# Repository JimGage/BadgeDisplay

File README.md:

# Badge Display

## Introduction
This was a bit of an art project that I did for SIGGRAPH 2018. Path tracing seemed to be a big theme that year and I wanted a badge that spent the day path tracing. The plan was that it would start off fuzzy in the morning and by the end of the day render a clear image.

## Images

The final badge

The images that were rendered during the first four days of the conference. Each image took around 10 hours on 72MHz ARM processor.

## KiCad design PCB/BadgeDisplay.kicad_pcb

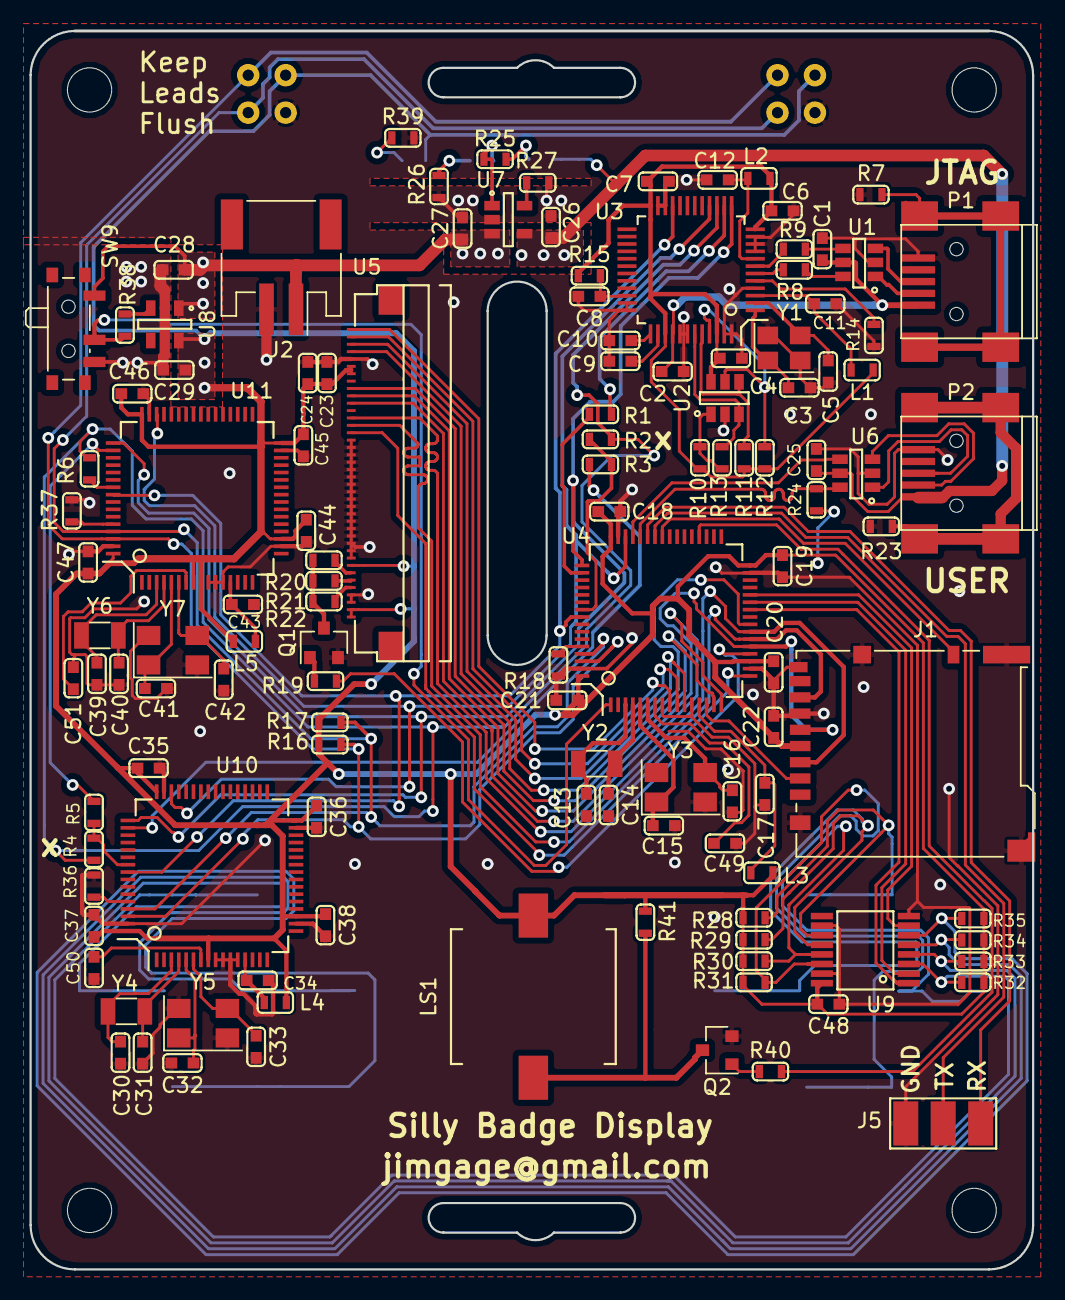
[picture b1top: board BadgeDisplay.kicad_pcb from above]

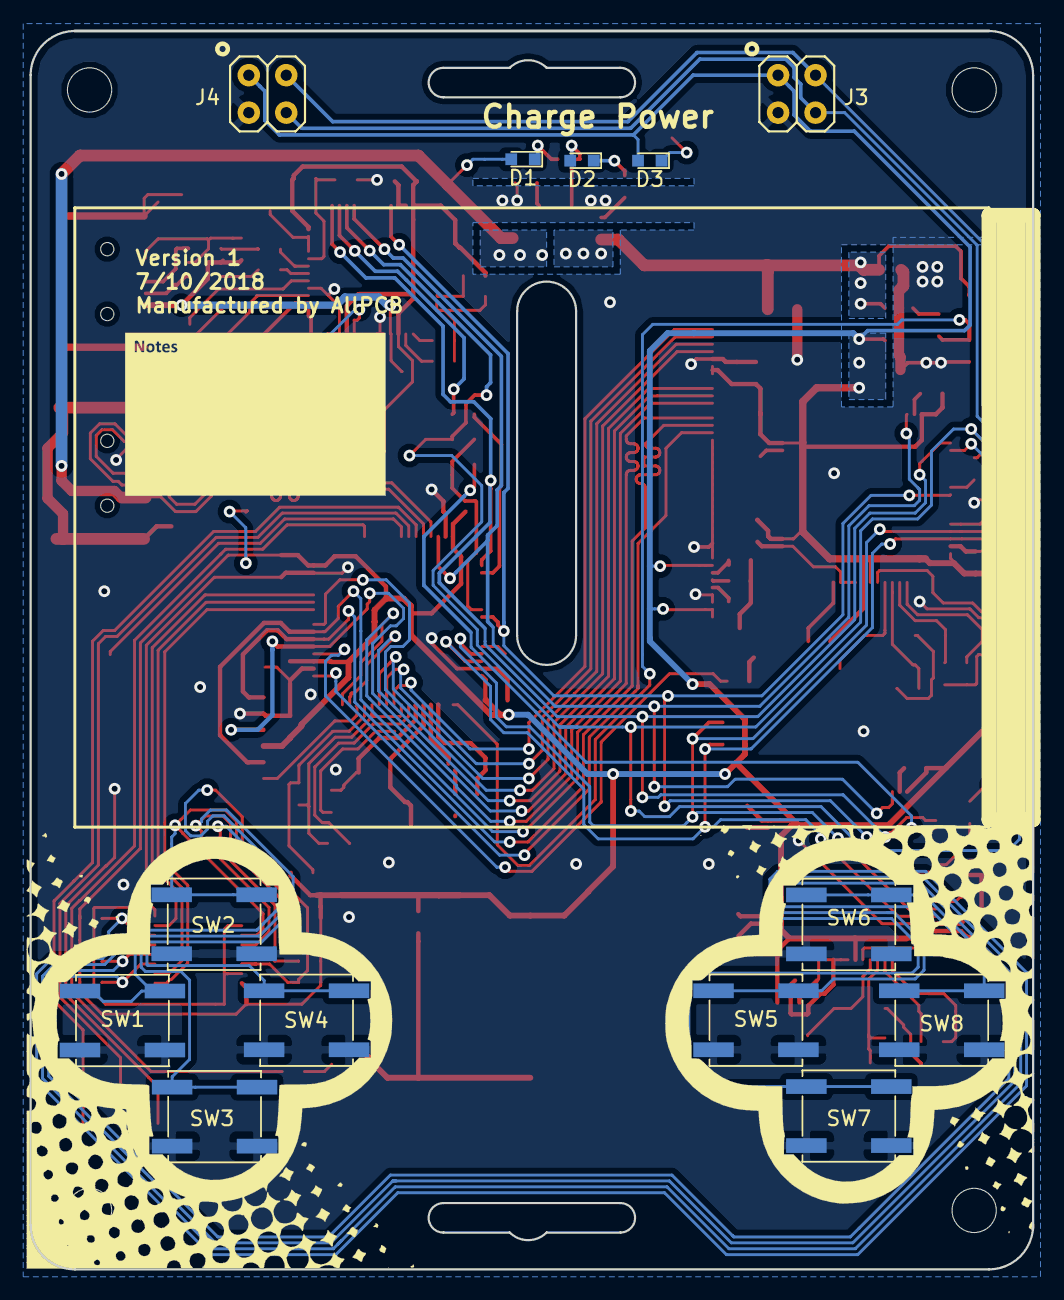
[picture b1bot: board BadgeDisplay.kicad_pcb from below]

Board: 2 copper layers, 68.0 x 84.0 mm, 137 parts (13 on the bottom side), 105 nets.

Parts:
C1, C4, C6, C7, C9, C10, C17, C18, C19, C20, C21, C22, C23, C25, C34, C35, C36, C37, C38, C43, C44, C45, C46, C47, C48, C49, C50, C51: 0u1; C_0603
C2, C11, C12, C26, C27, C28, C29: 4u7; C_0603
C3, C5: 16p; C_0603
C8: 10n; C_0603
C13, C14, C30, C31, C39, C40: 22p; C_0603
C15, C16, C32, C33, C41, C42: 36p; C_0603
C24: 1u; C_0603
D1, D2, D3: LED; LED_0603
J1: Micro_SD_Card_Det; Hirose_DM3BT-DSF-PEJS
J2: Conn_01x02; JST_PH_S2B-PH-SM4-TB_02x2.00mm_Angled
J3, J4: AddOn; AddOnConnector
J5: Conn_01x03; 3pin_smd
L1, L2, L3, L4, L5: Bead; L_0603
LS1: Speaker_Crystal; AST1109MLTRQ
P1, P2: USB_MINI; USB_Mini-B
Q1, Q2: MMBT3904; SOT-23
R1, R3, R5, R6: 0; R_0603
R2, R4: X; R_0603
R7, R23: 1; R_0603
R8, R9: 22; R_0603
R10, R11, R12, R15, R18, R28, R29, R30, R31, R32, R33, R34, R35, R36, R37: 10K; R_0603
R13: 2K; R_0603
R14: 12K; R_0603
R16, R17: 4k7; R_0603
R19, R40, R41: 1K; R_0603
R20, R21, R22, R38: 10; R_0603
R24: 1K5; R_0603
R25, R26: 470; R_0603
R27: 2k; R_0603
R39: 100; R_0603
SW1: LEFT_LEFT; SW_SPST_EVPBF
SW2: LEFT_UP; SW_SPST_EVPBF
SW3: LEFT_DOWN; SW_SPST_EVPBF
SW4: LEFT_RIGHT; SW_SPST_EVPBF
SW5: RIGHT_LEFT; SW_SPST_EVPBF
SW6: RIGHT_UP; SW_SPST_EVPBF
SW7: RIGHT_DOWN; SW_SPST_EVPBF
SW8: RIGHT_RIGHT; SW_SPST_EVPBF
SW9: SW_SPDT; SW_SPDT_PCM12
U1, U6: USBLC6-2; SOT-23-6
U2: 93LC56BT-OT; SOT-23-6
U3: FT232H; LQFP-48_7x7mm_Pitch0.5mm
U4, U10, U11: STM32F303RE-LQFP64; LQFP-64_10x10mm_Pitch0.5mm
U5: LCD_40PIN; 40Pin_conn_05Pitch
U7: MCP73831T; SOT-23-5
U8: TLV75733PDBVR; SOT-23-5
U9: 74HC165; TSSOP-16_4.4x5mm_Pitch0.65mm
Y1: 12MHz; Crystal_SMD_3225-4pin_3.2x2.5mm
Y2, Y4, Y6: 32.768KHz; Crystal_SMD_3215-2pin_3.2x1.5mm
Y3, Y5, Y7: 8MHz; Crystal_SMD_5032-4pin_5.0x3.2mm

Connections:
+3.3VA: C4.1, C6.1, C7.1, L1.2, L2.1, R10.1, R11.1, R12.1, R15.1, U2.6, U3.12, U3.24, U3.39, U3.46
+3V3: C18.1, C19.1, C20.1, C21.1, C22.1, C23.1, C24.1, C29.1, C35.1, C36.1, C37.1, C38.1, C44.1, C45.1, C46.1, C47.1, C48.1, D3.2, J1.4, J3.1, J4.1, L3.2, L4.2, L5.2, LS1.1, R16.1, R17.1, R24.1, R28.1, R29.1, R30.1, R31.1, R32.1, R33.1, R34.1, R35.1, R41.1, U4.19, U4.32, U4.48, U4.64, U5.6, U5.7, U5.33, U5.39, U5.40, U8.5, U9.16, U10.8, U10.19, U10.32, U10.48, U10.64, U11.8, U11.9, U11.19, U11.32, U11.48, U11.64
+5V: C25.1, C26.1, D1.2, P2.1, U6.5, U7.4
/FT232H/JTAG-TDI: R1.2, U3.14
/FT232H/JTAG-TDO: R2.2, R4.2, R6.1, U3.15
/JNTRST: U3.21, U4.56, U10.56, U11.56
/JTCK: U3.13, U4.49, U10.49, U11.49
/JTMS: U3.16, U4.46, U10.46, U11.46
/LCD_SD/BK_LIGHT: R19.2, U4.20
/LCD_SD/CARD_DETECT: J1.10, U4.41
/LCD_SD/CMD: U4.16, U5.11
/LCD_SD/LCD_CS: U4.15, U5.9
/LCD_SD/LCD_RESET: U4.17, U5.15
/LCD_SD/SCLK: J1.5, U4.21, U5.10
/LCD_SD/SD_CS: J1.2, U4.14
/Power/BATTERY: R38.2, SW9.2, U4.1
/Power/USB+: R24.2, U4.44, U6.6
/Power/USB-: U4.45, U6.4
/Power/VBAT: C27.1, C28.1, J2.1, SW9.1, U7.3, U8.1
/SCL: J3.3, J4.3, R17.2, U4.61, U10.61, U11.61
/SDA: J3.4, J4.4, R16.2, U4.62, U10.62, U11.62
/STM_Master/ANALOG0: U4.9, U5.1
/STM_Master/ANALOG1: U4.10, U5.2
/STM_Master/ANALOG2: U4.11, U5.3
/STM_Master/ANALOG3: U4.24, U5.4
/STM_Master/BUTTON_CLOCK: U4.27, U9.2
/STM_Master/BUTTON_DATA: U4.28, U9.7
/STM_Master/BUTTON_LATCH: U4.26, U9.1
/STM_Master/JTDI: R1.1, U4.50
/STM_Master/JTDO: R2.1, R3.2, U4.55
/STM_Master/MISO: J1.7, U4.22, U5.14
/STM_Master/MOSI: J1.3, U4.23, U5.13
/STM_Master/NRST: C49.1, U4.7
/STM_Master/USART1_RX: J5.1, U4.43
/STM_Master/USART1_TX: J5.2, U4.42
/STM_SLAVE0/JTDI: R3.1, U10.50
/STM_SLAVE0/JTDO: R4.1, R5.2, U10.55
/STM_SLAVE0/NRST: C50.1, U10.7
/STM_SLAVE1/JTDI: R5.1, U11.50
/STM_SLAVE1/JTDO: R6.2, U11.55
/STM_SLAVE1/NRST: C51.1, U11.7
GND: C1.2, C2.2, C3.2, C4.2, C5.2, C6.2, C7.2, C8.2, C9.2, C10.2, C11.2, C12.2, C13.2, C14.2, C15.2, C16.2, C17.2, C18.2, C19.2, C20.2, C21.2, C22.2, C23.2, C24.2, C25.2, C26.2, C27.2, C28.2, C29.2, C30.2, C31.2, C32.2, C33.2, C34.2, C35.2, C36.2, C37.2, C38.2, C39.2, C40.2, C41.2, C42.2, C43.2, C44.2, C45.2, C46.2, C47.2, C48.2, C49.2, C50.2, C51.2, J1.6, J1.9, J1.11, J2.2, J3.2, J4.2, J5.3, P1.5, P2.5, Q1.2, Q2.2, R7.1, R14.1, R18.1, R23.1, R26.2, R27.2, R36.1, R37.1, R39.2, SW1.1, SW2.1, SW3.1, SW4.1, SW5.1, SW6.1, SW7.1, SW8.1, SW9.3, U1.2, U2.2, U3.4, U3.9, U3.10, U3.11, U3.22, U3.23, U3.35, U3.36, U3.41, U3.42, U3.47, U3.48, U4.8, U4.12, U4.18, U4.31, U4.47, U4.63, U5.5, U5.16, U5.17, U5.18, U5.19, U5.20, U5.21, U5.22, U5.23, U5.24, U5.25, U5.26, U5.27, U5.28, U5.29, U5.30, U5.31, U5.32, U5.37, U5.38, U6.2, U7.2, U8.2, U9.8, U9.10, U9.15, U10.9, U10.10, U10.11, U10.12, U10.18, U10.31, U10.47, U10.63, U11.10, U11.11, U11.12, U11.18, U11.31, U11.47, U11.63, Y1.2, Y1.4, Y3.2, Y3.4, Y5.2, Y5.4, Y7.2, Y7.4
unnamed: C1.1, C2.1, P1.1, U1.5, U3.40
unnamed: C3.1, U3.1, Y1.1
unnamed: C5.1, U3.2, Y1.3
unnamed: C8.1, R15.2, U3.34
unnamed: C9.1, U3.38
unnamed: C10.1, U3.37
unnamed: C11.1, L1.1, U3.3
unnamed: C12.1, L2.2, U3.8
unnamed: C13.1, U4.3, Y2.1
unnamed: C14.1, U4.4, Y2.2
unnamed: C15.1, U4.5, Y3.1
unnamed: C16.1, U4.6, Y3.3
unnamed: C17.1, L3.1, U4.13
unnamed: C30.1, U10.3, Y4.1
unnamed: C31.1, U10.4, Y4.2
unnamed: C32.1, U10.5, Y5.1
unnamed: C33.1, U10.6, Y5.3
unnamed: C34.1, L4.1, U10.13
unnamed: C39.1, U11.3, Y6.1
unnamed: C40.1, U11.4, Y6.2
unnamed: C41.1, U11.5, Y7.1
unnamed: C42.1, U11.6, Y7.3
unnamed: C43.1, L5.1, U11.13
unnamed: D1.1, R25.1
unnamed: D2.1, R26.1
unnamed: D2.2, R25.2, U7.1
unnamed: D3.1, R39.1
unnamed: LS1.2, Q2.3, R41.2
unnamed: P1.2, U1.1
unnamed: P1.3, U1.3
unnamed: P1.6, R7.2
unnamed: P2.2, U6.3
unnamed: P2.3, U6.1
unnamed: P2.6, R23.2
unnamed: Q1.1, R19.1
unnamed: Q1.3, R20.2, R21.2, R22.2
unnamed: Q2.1, R40.1
unnamed: R8.1, U3.6
unnamed: R8.2, U1.6
unnamed: R9.1, U3.7
unnamed: R9.2, U1.4
unnamed: R10.2, R13.2, U2.1
unnamed: R11.2, U2.4, U3.44
unnamed: R12.2, U2.5, U3.45
unnamed: R13.1, U2.3, U3.43
unnamed: R14.2, U3.5
unnamed: R18.2, U4.60
unnamed: R20.1, U5.34
unnamed: R21.1, U5.35
unnamed: R22.1, U5.36
unnamed: R27.1, U7.5
unnamed: R28.2, SW2.2, U9.11
unnamed: R29.2, SW4.2, U9.12
unnamed: R30.2, SW1.2, U9.13
unnamed: R31.2, SW3.2, U9.14
unnamed: R32.2, SW6.2, U9.3
unnamed: R33.2, SW8.2, U9.4
unnamed: R34.2, SW5.2, U9.5
unnamed: R35.2, SW7.2, U9.6
unnamed: R36.2, U10.60
unnamed: R37.2, U11.60
unnamed: R38.1, U8.3
unnamed: R40.2, U4.36

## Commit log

2025-03-01 Images for readme
2025-03-01 Create README.md
    Created the initial readme for the project
